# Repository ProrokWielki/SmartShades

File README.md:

# SmartShades

ESP-12F based project which enables to convert any standard shades into smart shades.

It communicates using mqtt and allows controlling the shades position

### What you need

* ESP-12F - or compatible device
* DRV8220DSG
* motor with encoder
* LM117-3.3
* capacitors and resistors

###

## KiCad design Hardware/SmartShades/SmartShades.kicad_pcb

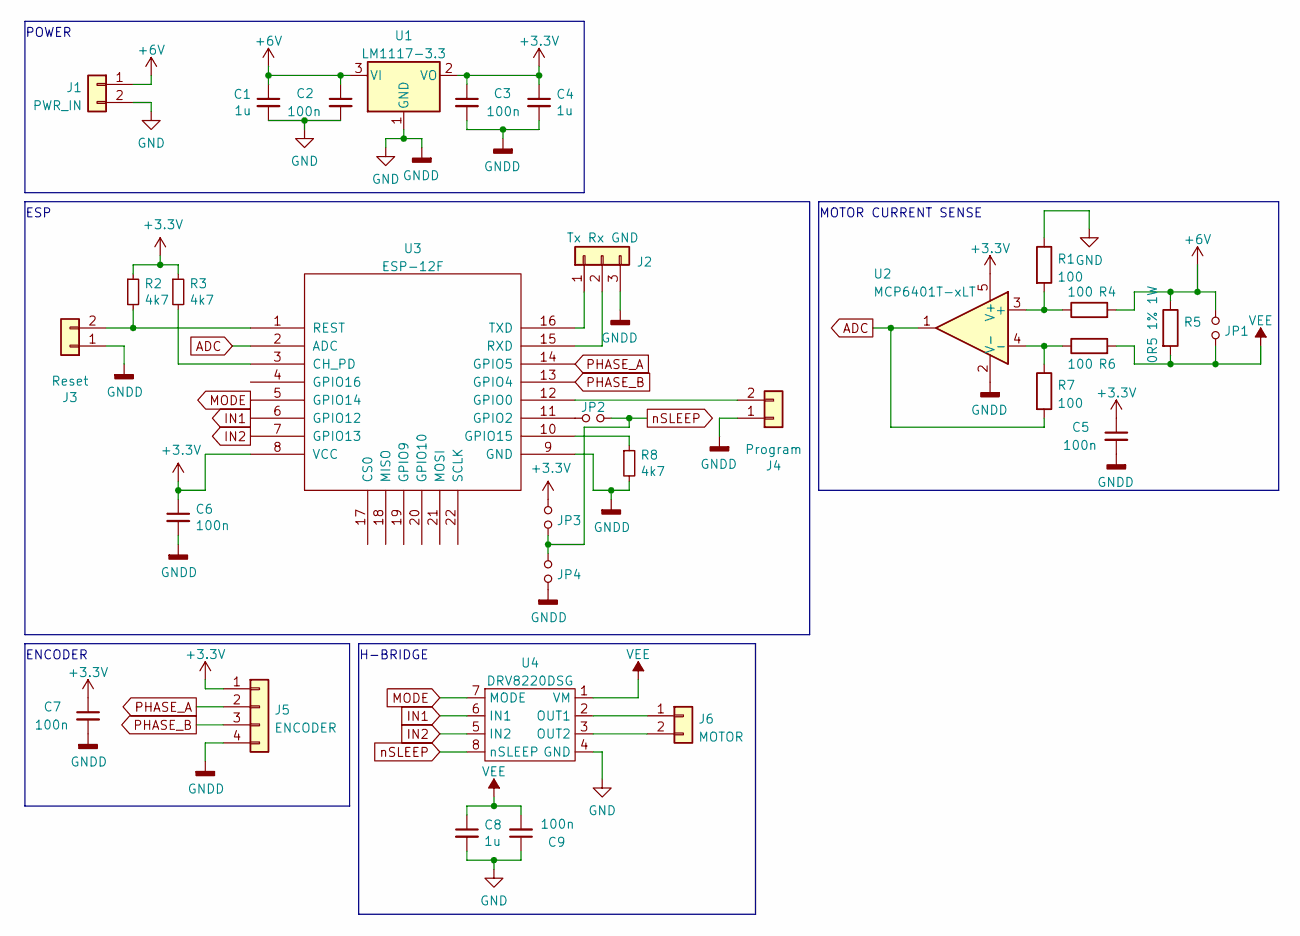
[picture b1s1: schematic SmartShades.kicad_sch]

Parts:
C1, C4, C8: 1u; C_0805_2012Metric
C2, C3, C5, C6, C7, C9: 100n; C_0805_2012Metric
J1: PWR_IN; TerminalBlock_Altech_AK300-2_P5.00mm
J2: Tx Rx GND; Harwin_M20-89003xx_1x03_P2.54mm_Horizontal
J3: Reset; SolderJumper-2_P1.3mm_Open_RoundedPad1.0x1.5mm
J4: Program; SolderJumper-2_P1.3mm_Open_RoundedPad1.0x1.5mm
J5: ENCODER; Harwin_M20-89004xx_1x04_P2.54mm_Horizontal
J6: MOTOR; Harwin_M20-89003xx_1x03_P2.54mm_Horizontal
JP1, JP2, JP3, JP4: Jumper_NO_Small; SolderJumper-2_P1.3mm_Open_RoundedPad1.0x1.5mm
R1, R4, R6, R7: 100; R_0805_2012Metric
R2, R3, R8: 4k7; R_0805_2012Metric
R5: 0R5 1% 1W; R_1206_3216Metric
U1: LM1117-3.3; SOT-223-3_TabPin2
U2: MCP6401T-xLT; SOT-353_SC-70-5
U3: ESP-12F; ESP-12E_SMD
U4: DRV8220DSG; WSON-8-1EP_2x2mm_P0.5mm_EP0.9x1.6mm

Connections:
+3V3: C3.1, C4.1, C5.1, C6.1, C7.1, J5.1, JP3.1, R2.1, R3.1, U1.2 (VO), U2.5 (V+), U3.8 (VCC)
+6V: C1.1, C2.1, J1.1, JP1.1, R4.2, R5.1, U1.3 (VI)
ADC: R7.2, U2.1, U3.2 (ADC)
GND: C1.2, C2.2, C3.2, C4.2, C5.2, C6.2, C7.2, C8.2, C9.1, J1.2, J2.3, J3.1, J4.1, J5.4, JP4.2, R1.1, R8.2, U1.1 (GND), U2.2 (V-), U3.9 (GND), U4.4 (GND), U4.9 (Pad)
IN1: U3.6 (GPIO12), U4.6 (IN1)
IN2: U3.7 (GPIO13), U4.5 (IN2)
MODE: U3.5 (GPIO14), U4.7 (MODE)
unnamed: J6.1, U4.2 (OUT1)
unnamed: J6.2, U4.3 (OUT2)
unnamed: JP2.1, U3.11 (GPIO2)
unnamed: R1.2, R4.1, U2.3 (+)
unnamed: R6.1, R7.1, U2.4 (-)
unnamed: J3.2, R2.2, U3.1 (REST)
unnamed: R3.2, U3.3 (CH_PD)
unnamed: R8.1, U3.10 (GPIO15)
unnamed: J4.2, U3.12 (GPIO0)
unnamed: J2.2, U3.15 (RXD)
unnamed: J2.1, U3.16 (TXD)
PHASE_A: J5.2, U3.14 (GPIO5)
PHASE_B: J5.3, U3.13 (GPIO4)
VEE: C8.1, C9.2, JP1.2, R5.2, R6.2, U4.1 (VM)
nSLEEP: JP2.2, JP3.2, JP4.1, U4.8 (nSLEEP)

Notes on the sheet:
POWER
MOTOR CURRENT SENSE
ENCODER
H-BRIDGE
ESP

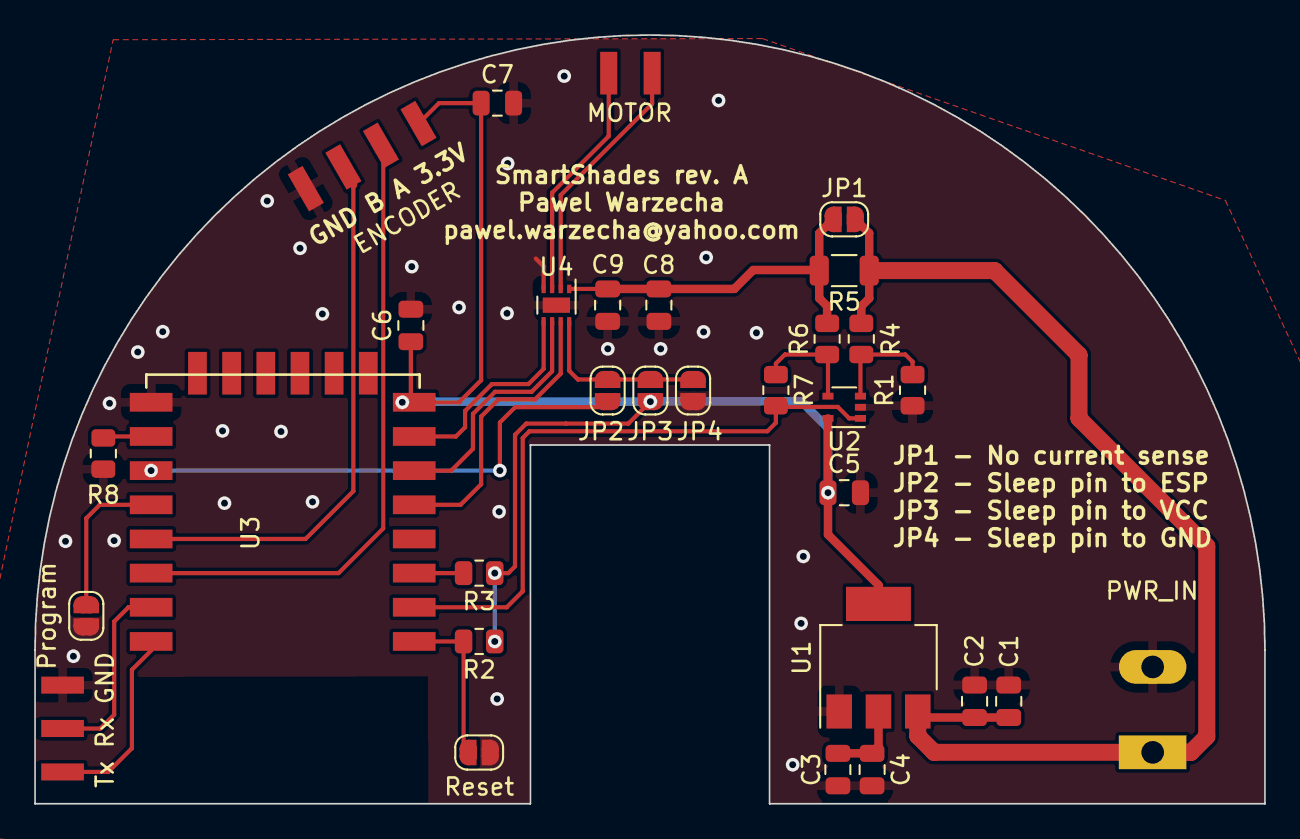
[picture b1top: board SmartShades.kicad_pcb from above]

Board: 2 copper layers, 72.0 x 45.0 mm, 31 parts (0 on the bottom side), 22 nets.

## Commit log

2023-05-27 Schematics for the SmartShades
2023-05-28 Added net file
2023-05-28 Added pcb
2023-05-28 added Changelog file
2023-05-28 Moved Hardware files one level up
2023-05-28 Gerber files added
2024-04-12 added esp_utils submodule
2024-04-12 added .gitignore
2024-04-13 added clang-format config
2024-04-13 added config for drv8220dsg
2024-04-13 added config for encoder
2024-04-13 added config file
2024-04-13 added state machine
2024-04-13 added ino file
2024-04-13 added README
